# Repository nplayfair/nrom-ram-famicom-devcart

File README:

NROM/CNROM/GNROM+PRG RAM Nintendo Famicom Devcart.

Original developer: Krzysztof Iwanowski

The PCB layouts and schematics are released under a Creative Commons cc-by-sa 3.0 license.

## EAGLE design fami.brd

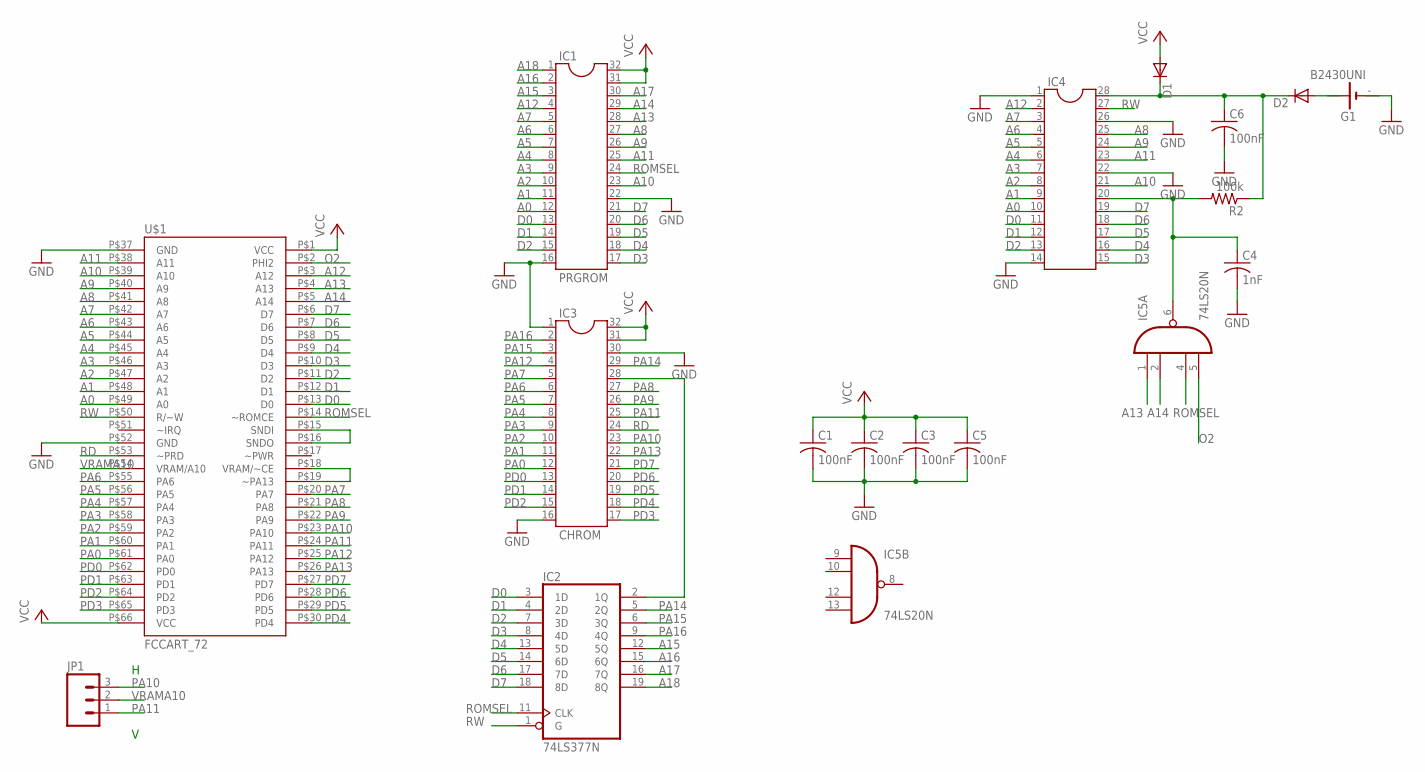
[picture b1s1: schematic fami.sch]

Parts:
C1, C2, C3, C5, C6: 100nF; C025-025X050
C4: 1nF; C025-025X050
D1, D2: DIODE-D-5; D-5
G1: B2430UNI
IC1: PRGROM; DIL32
IC2: 74LS377N; DIL20
IC3: CHROM; DIL32
IC4: DIL28; DIL28-6
IC5: 74LS20N; DIL14
JP1: M03PTH; 1X03
R2: 100k; 0204/7
U$1: FCCART_72

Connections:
A0: IC1.12, IC4.10, U$1.P$49 (A0)
A1: IC1.11, IC4.9, U$1.P$48 (A1)
A2: IC1.10, IC4.8, U$1.P$47 (A2)
A3: IC1.9, IC4.7, U$1.P$46 (A3)
A4: IC1.8, IC4.6, U$1.P$45 (A4)
A5: IC1.7, IC4.5, U$1.P$44 (A5)
A6: IC1.6, IC4.4, U$1.P$43 (A6)
A7: IC1.5, IC4.3, U$1.P$42 (A7)
A8: IC1.27, IC4.25, U$1.P$41 (A8)
A9: IC1.26, IC4.24, U$1.P$40 (A9)
A10: IC1.23, IC4.21, U$1.P$39 (A10)
A11: IC1.25, IC4.23, U$1.P$38 (A11)
A12: IC1.4, IC4.2, U$1.P$3 (A12)
A13: IC1.28, IC5.1 (I0), U$1.P$4 (A13)
A14: IC1.29, IC5.2 (I1), U$1.P$5 (A14)
A15: IC1.3, IC2.12 (5Q)
A16: IC1.2, IC2.15 (6Q)
A17: IC1.30, IC2.16 (7Q)
A18: IC1.1, IC2.19 (8Q)
D0: IC1.13, IC2.3 (1D), IC4.11, U$1.P$13 (D0)
D1: IC1.14, IC2.4 (2D), IC4.12, U$1.P$12 (D1)
D2: IC1.15, IC2.7 (3D), IC4.13, U$1.P$11 (D2)
D3: IC1.17, IC2.8 (4D), IC4.15, U$1.P$10 (D3)
D4: IC1.18, IC2.13 (5D), IC4.16, U$1.P$9 (D4)
D5: IC1.19, IC2.14 (6D), IC4.17, U$1.P$8 (D5)
D6: IC1.20, IC2.17 (7D), IC4.18, U$1.P$7 (D6)
D7: IC1.21, IC2.18 (8D), IC4.19, U$1.P$6 (D7)
GND: C1.2, C2.2, C3.2, C4.2, C5.2, C6.2, G1.-, G1.-@1 (-), IC1.16, IC1.22, IC2.10 (GND), IC3.1, IC3.16, IC3.30, IC4.1, IC4.14, IC4.22, IC4.26, IC5.7 (GND), U$1.P$37 (GND), U$1.P$52 (GND)
unnamed: IC2.2 (1Q), IC3.28
unnamed: U$1.P$15 (SNDI), U$1.P$16 (SNDO)
unnamed: U$1.P$18 (VRAM/~CE), U$1.P$19 (~PA13)
unnamed: C6.1, D1.C, D2.C, IC4.28, R2.1
unnamed: C4.1, IC4.20, IC5.6 (O), R2.2
unnamed: D2.A, G1.+@4 (+)
O2: IC5.5 (I3), U$1.P$2 (PHI2)
PA0: IC3.12, U$1.P$61 (PA0)
PA1: IC3.11, U$1.P$60 (PA1)
PA2: IC3.10, U$1.P$59 (PA2)
PA3: IC3.9, U$1.P$58 (PA3)
PA4: IC3.8, U$1.P$57 (PA4)
PA5: IC3.7, U$1.P$56 (PA5)
PA6: IC3.6, U$1.P$55 (PA6)
PA7: IC3.5, U$1.P$20 (PA7)
PA8: IC3.27, U$1.P$21 (PA8)
PA9: IC3.26, U$1.P$22 (PA9)
PA10: IC3.23, JP1.3, U$1.P$23 (PA10)
PA11: IC3.25, JP1.1, U$1.P$24 (PA11)
PA12: IC3.4, U$1.P$25 (PA12)
PA13: IC3.22, U$1.P$26 (PA13)
PA14: IC2.5 (2Q), IC3.29
PA15: IC2.6 (3Q), IC3.3
PA16: IC2.9 (4Q), IC3.2
PD0: IC3.13, U$1.P$62 (PD0)
PD1: IC3.14, U$1.P$63 (PD1)
PD2: IC3.15, U$1.P$64 (PD2)
PD3: IC3.17, U$1.P$65 (PD3)
PD4: IC3.18, U$1.P$30 (PD4)
PD5: IC3.19, U$1.P$29 (PD5)
PD6: IC3.20, U$1.P$28 (PD6)
PD7: IC3.21, U$1.P$27 (PD7)
RD: IC3.24, U$1.P$53 (~PRD)
ROMSEL: IC1.24, IC2.11 (CLK), IC5.4 (I2), U$1.P$14 (~ROMCE)
RW: IC2.1 (G), IC4.27, U$1.P$50 (R/~W)
VCC: C1.1, C2.1, C3.1, C5.1, D1.A, IC1.31, IC1.32, IC2.20 (VCC), IC3.31, IC3.32, IC5.14 (VCC), U$1.P$1 (VCC), U$1.P$66 (VCC)
VRAMA10: JP1.2, U$1.P$54 (VRAM/A10)

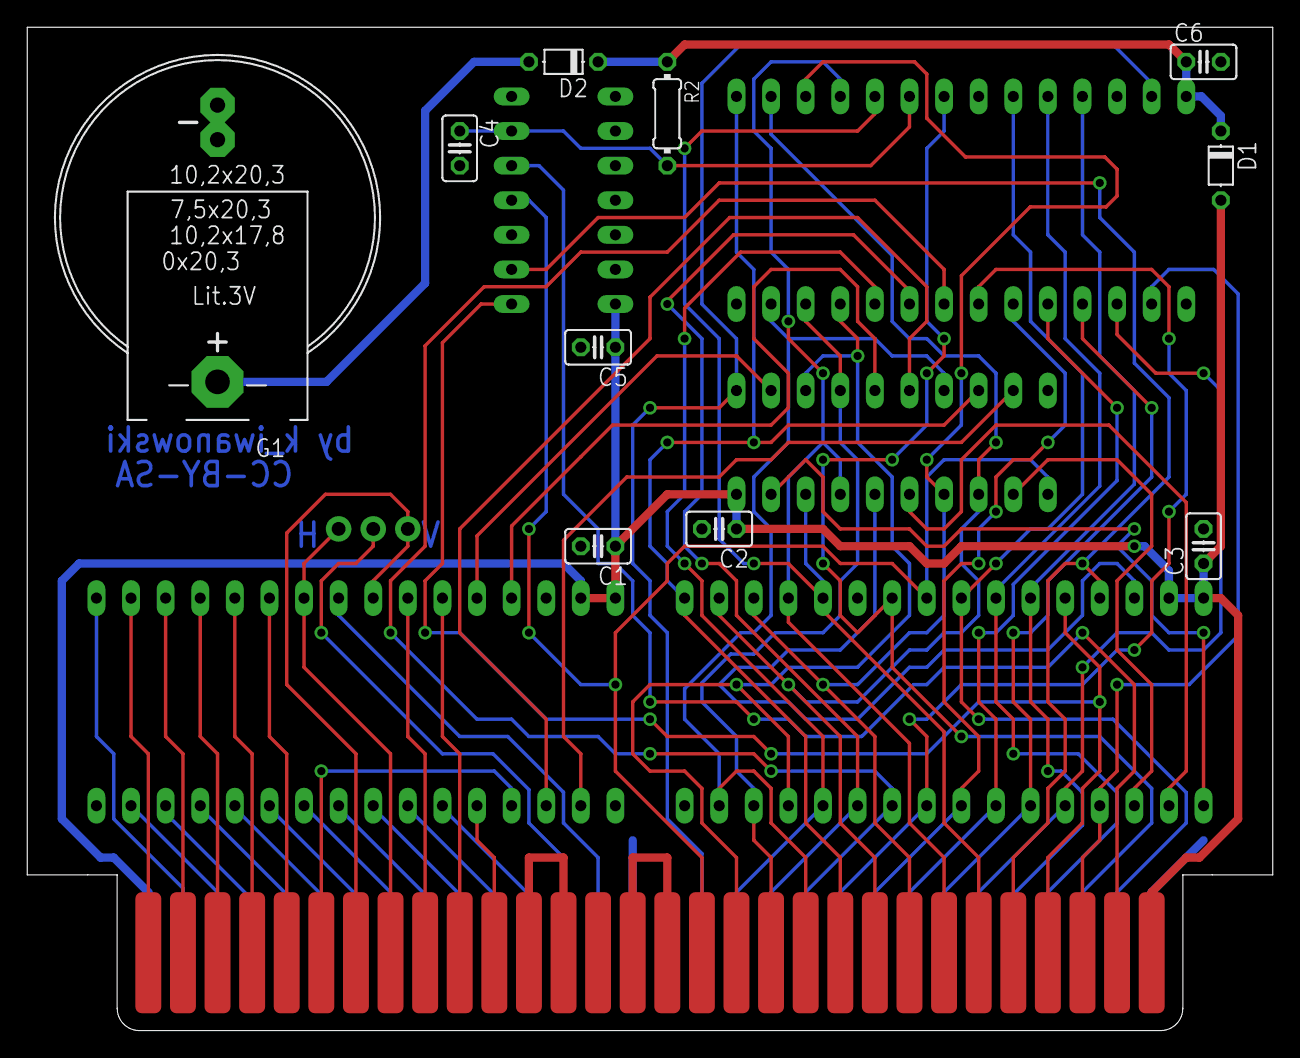
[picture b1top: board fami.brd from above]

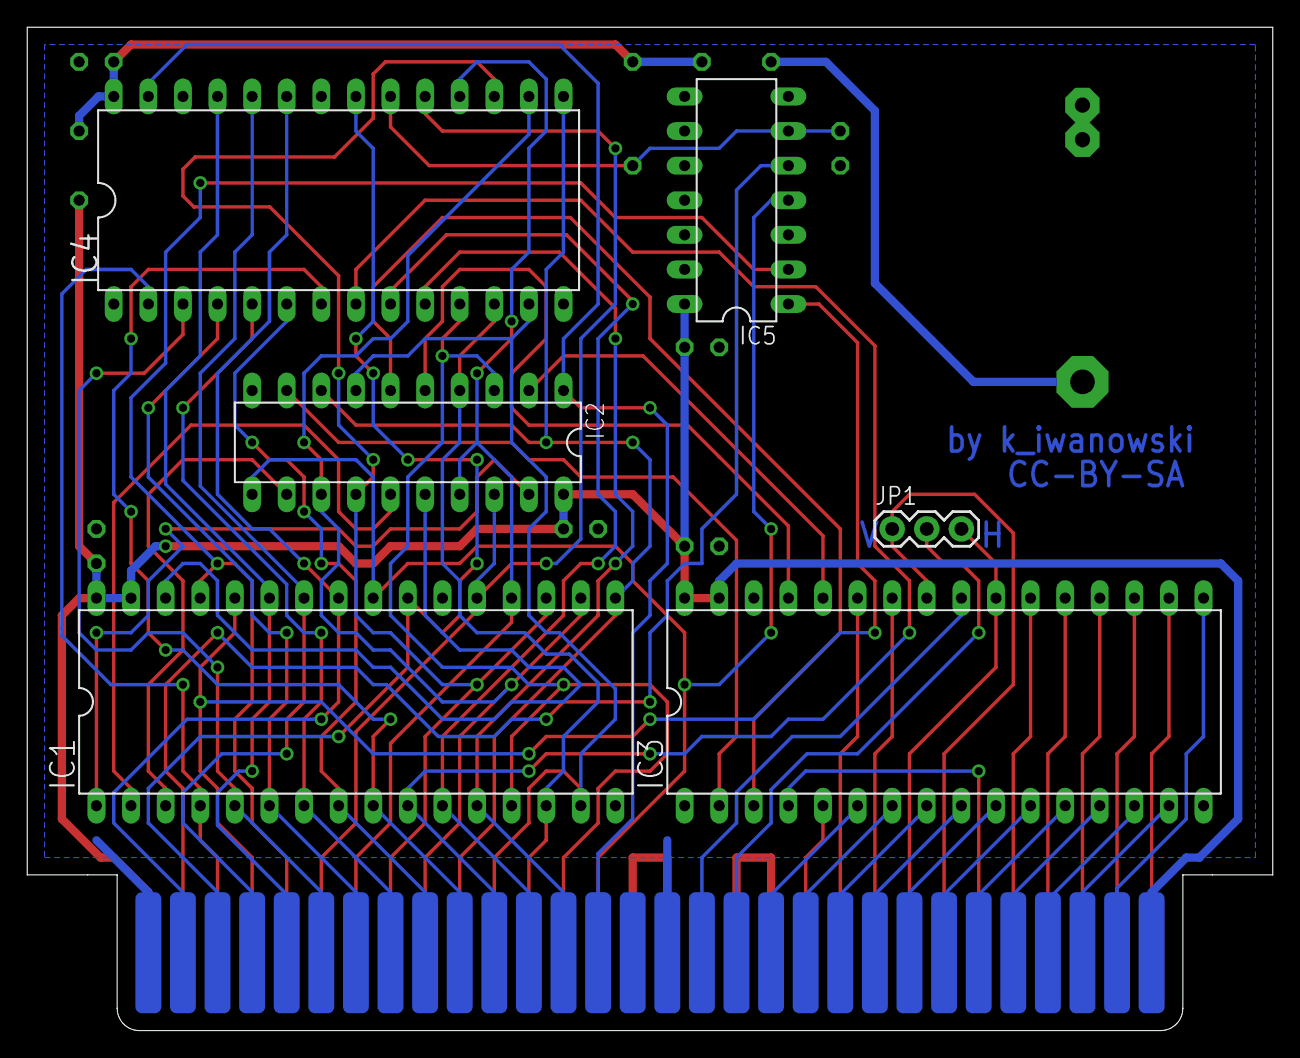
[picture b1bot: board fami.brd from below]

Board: 2 copper layers, 91.4 x 73.7 mm, 17 parts (6 on the bottom side), 65 nets.

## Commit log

2016-07-22 :lollipop: Added .gitattributes & .gitignore files
2016-07-22 optimized the pcb a little bit
2016-07-22 added credits to the pcb
2016-07-24 Added R and C values
2017-08-29 Added support for CNROM and GNROM

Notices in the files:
parts and their libraries:
SparkFun-Connectors: Licensing: Creative Commons ShareAlike 4.0 International - https://creativecommons.org/licenses/by-sa/4.0
